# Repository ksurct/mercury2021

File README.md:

# mercury2021
KSURCT's repo for the 2021 OSU Mercury Robotics Challenge

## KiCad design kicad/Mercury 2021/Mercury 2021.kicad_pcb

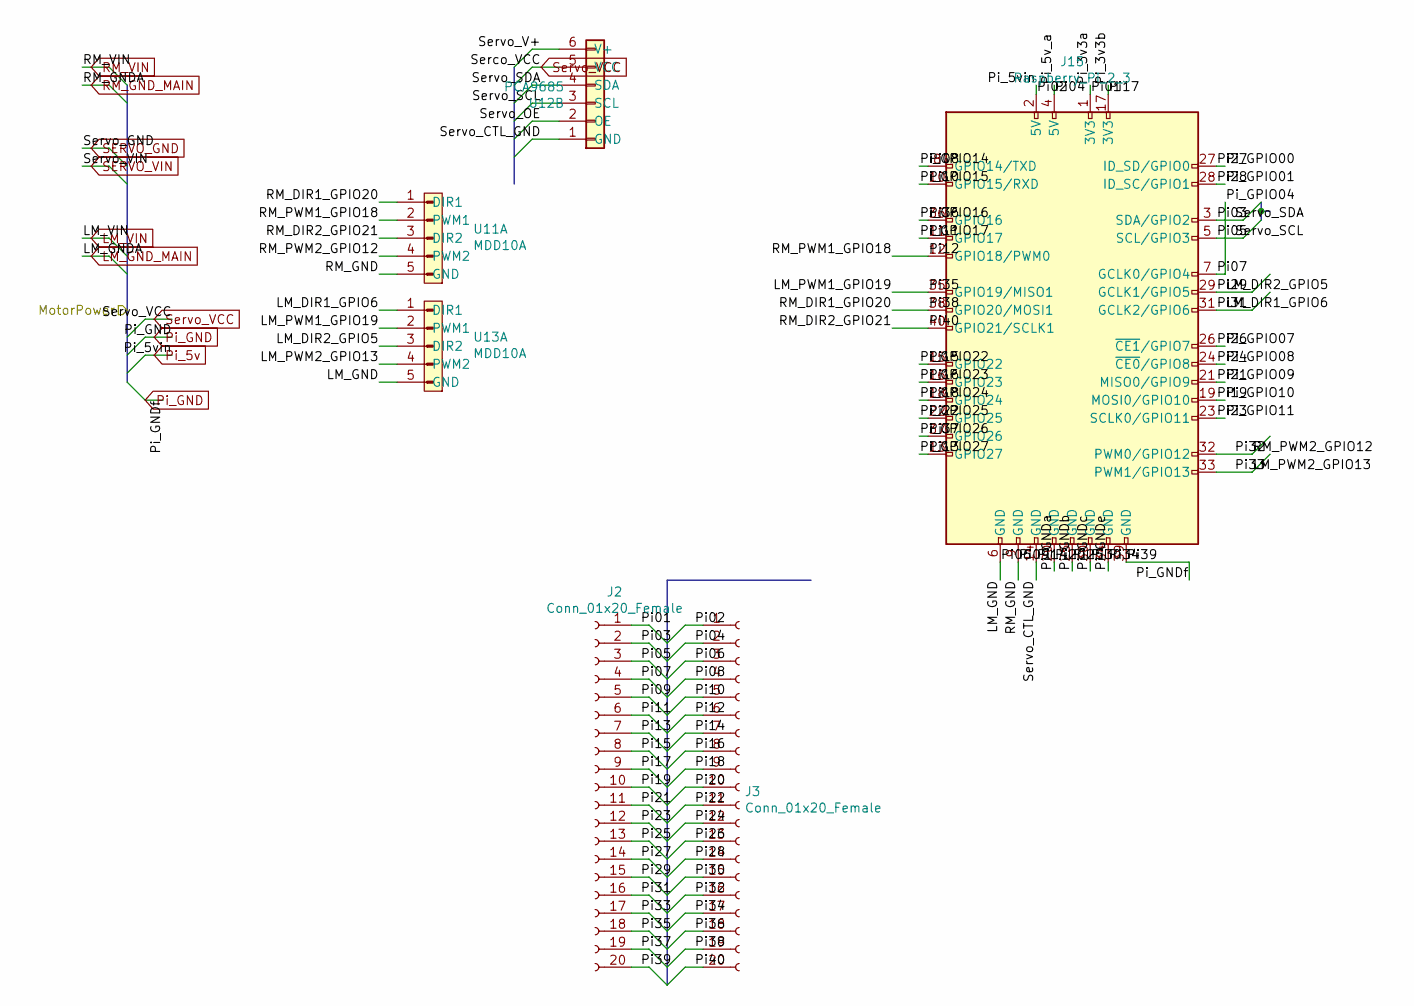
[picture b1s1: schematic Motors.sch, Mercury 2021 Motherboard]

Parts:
J2, J3: Conn_01x20_Female; PinSocket_1x20_P2.54mm_Vertical
J15: Raspberry_Pi_2_3; PinSocket_2x20_P2.54mm_Vertical
U11, U13: MDD10A; PinSocket_1x05_P2.54mm_Vertical
U12: PCA9685; PinSocket_1x06_P2.54mm_Vertical

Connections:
5v_Rail: J3.1, J15.2 (5V), U12.5 (VCC); also elsewhere on the board
/Motors/LM_DIR1_GPIO6: J2.16, J15.31 (GCLK2/GPIO6), U13.1 (DIR1)
/Motors/LM_DIR2_GPIO5: J2.15, J15.29 (GCLK1/GPIO5), U13.3 (DIR2)
/Motors/LM_GND: J3.3, J15.6 (GND), U13.5 (GND)
/Motors/LM_PWM1_GPIO19: J2.18, J15.35 (GPIO19/MISO1), U13.2 (PWM1)
/Motors/LM_PWM2_GPIO13: J2.17, J15.33 (PWM1/GPIO13), U13.4 (PWM2)
/Motors/Pi01: J2.1, J15.1 (3V3)
/Motors/Pi03: J2.2, J15.3 (SDA/GPIO2), U12.4 (SDA)
/Motors/Pi04: J3.2, J15.4 (5V)
/Motors/Pi05: J2.3, J15.5 (SCL/GPIO3), U12.3 (SCL)
/Motors/Pi07: J2.4, J15.7 (GCLK0/GPIO4)
/Motors/Pi08: J3.4, J15.8 (GPIO14/TXD)
/Motors/Pi09: J2.5, J15.9 (GND), U11.5 (GND)
/Motors/Pi10: J3.5, J15.10 (GPIO15/RXD)
/Motors/Pi11: J2.6, J15.11 (GPIO17)
/Motors/Pi12: J3.6, J15.12 (GPIO18/PWM0), U11.2 (PWM1)
/Motors/Pi13: J2.7, J15.13 (GPIO27)
/Motors/Pi14: J3.7, J15.14 (GND), U12.1 (GND)
/Motors/Pi15: J2.8, J15.15 (GPIO22)
/Motors/Pi16: J3.8, J15.16 (GPIO23)
/Motors/Pi17: J2.9, J15.17 (3V3)
/Motors/Pi18: J3.9, J15.18 (GPIO24)
/Motors/Pi19: J2.10, J15.19 (MOSI0/GPIO10)
/Motors/Pi20: J3.10, J15.20 (GND)
/Motors/Pi21: J2.11, J15.21 (MISO0/GPIO9)
/Motors/Pi22: J3.11, J15.22 (GPIO25)
/Motors/Pi23: J2.12, J15.23 (SCLK0/GPIO11)
/Motors/Pi24: J3.12, J15.24 (~CE0~/GPIO8)
/Motors/Pi25: J2.13, J15.25 (GND)
/Motors/Pi26: J3.13, J15.26 (~CE1~/GPIO7)
/Motors/Pi27: J2.14, J15.27 (ID_SD/GPIO0)
/Motors/Pi28: J3.14, J15.28 (ID_SC/GPIO1)
/Motors/Pi30: J3.15, J15.30 (GND)
/Motors/Pi32: J3.16, J15.32 (PWM0/GPIO12), U11.4 (PWM2)
/Motors/Pi34: J3.17, J15.34 (GND)
/Motors/Pi36: J3.18, J15.36 (GPIO16)
/Motors/Pi37: J2.19, J15.37 (GPIO26)
/Motors/Pi38: J3.19, J15.38 (GPIO20/MOSI1), U11.1 (DIR1)
/Motors/Pi40: J3.20, J15.40 (GPIO21/SCLK1), U11.3 (DIR2)
/Motors/Servo_OE: U12.2 (OE)
/Motors/Servo_V+: U12.6 (V+)
GND_Rail: J2.20, J15.39 (GND); also elsewhere on the board

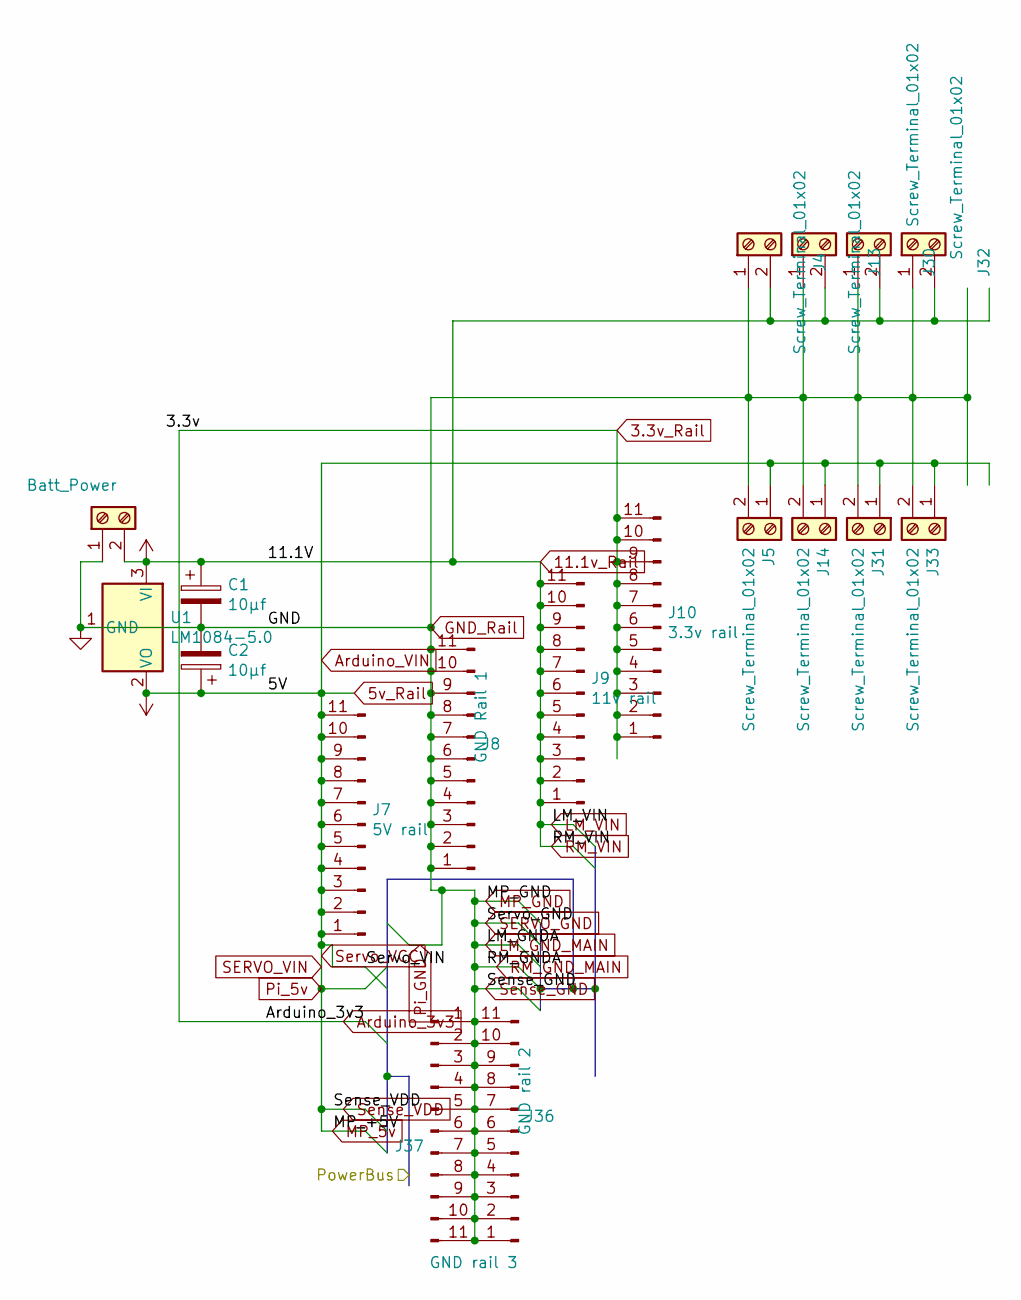
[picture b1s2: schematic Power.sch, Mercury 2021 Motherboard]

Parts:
C1, C2: 10μf; CP_Radial_D10.0mm_P2.50mm
J1: Batt_Power; TerminalBlock_Altech_AK300-2_P5.00mm
J4, J5, J13, J14, J30, J31, J32, J33: Screw_Terminal_01x02; TerminalBlock_Altech_AK300-2_P5.00mm
J7: 5V rail; PinHeader_1x11_P2.54mm_Vertical
J8: GND Rail 1; PinHeader_1x11_P2.54mm_Vertical
J9: 11v rail; PinHeader_1x11_P2.54mm_Vertical
J10: 3.3v rail; PinHeader_1x11_P2.54mm_Vertical
J36: GND rail 2; PinHeader_1x11_P2.54mm_Vertical
J37: GND rail 3; PinHeader_1x11_P2.54mm_Vertical
U1: LM1084-5.0; LM1084

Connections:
3.3v_Rail: J10.1, J10.2, J10.3, J10.4, J10.5, J10.6, J10.7, J10.8, J10.9, J10.10, J10.11; also elsewhere on the board
5v_Rail: C2.1, J5.1, J7.1, J7.2, J7.3, J7.4, J7.5, J7.6, J7.7, J7.8, J7.9, J7.10, J7.11, J14.1, J31.1, J33.1, U1.2 (VO); also elsewhere on the board
11.1v_Rail: C1.1, J1.2, J4.2, J9.1, J9.2, J9.3, J9.4, J9.5, J9.6, J9.7, J9.8, J9.9, J9.10, J9.11, J13.2, J30.2, J32.2, U1.3 (VI)
GND_Rail: C1.2, C2.2, J1.1, J4.1, J5.2, J8.1, J8.2, J8.3, J8.4, J8.5, J8.6, J8.7, J8.8, J8.9, J8.10, J8.11, J13.1, J14.2, J30.1, J31.2, J32.1, J33.2, J36.1, J36.2, J36.3, J36.4, J36.5, J36.6, J36.7, J36.8, J36.9, J36.10, J36.11, J37.1, J37.2, J37.3, J37.4, J37.5, J37.6, J37.7, J37.8, J37.9, J37.10, J37.11, U1.1 (GND); also elsewhere on the board

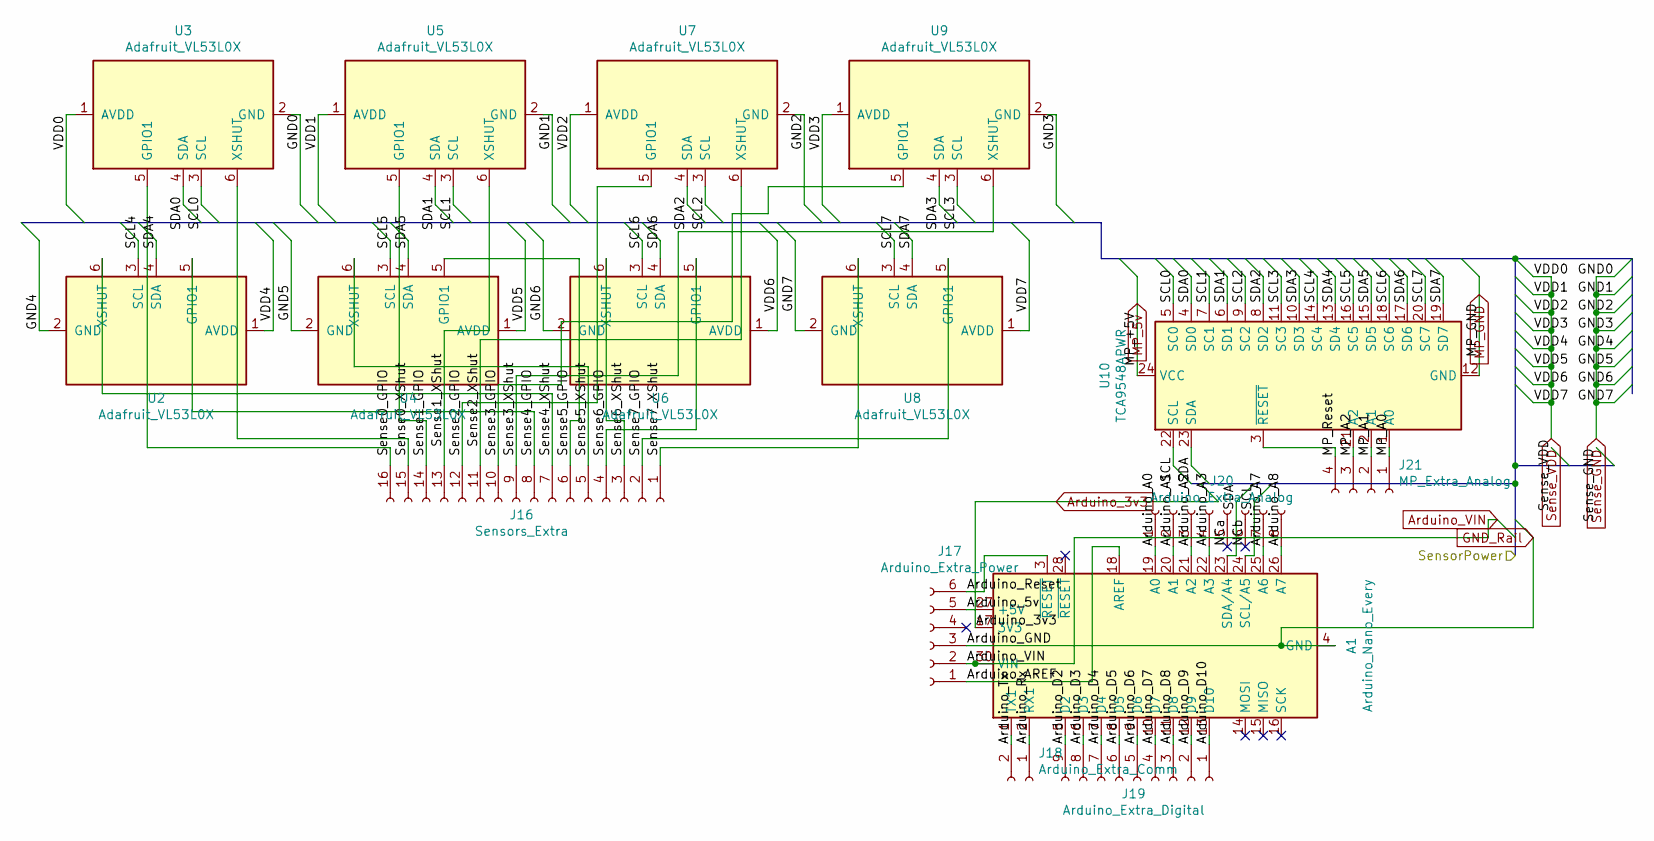
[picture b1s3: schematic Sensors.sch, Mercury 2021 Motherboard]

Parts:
A1: Arduino_Nano_Every; Arduino_Nano_WithMountingHoles
J16: Sensors_Extra; PinSocket_1x16_P2.54mm_Vertical
J17: Arduino_Extra_Power; PinSocket_1x06_P2.54mm_Vertical
J18: Arduino_Extra_Comm; PinSocket_1x02_P2.54mm_Vertical
J19: Arduino_Extra_Digital; PinSocket_1x09_P2.54mm_Vertical
J20: Arduino_Extra_Analog; PinSocket_1x08_P2.54mm_Vertical
J21: MP_Extra_Analog; PinSocket_1x04_P2.54mm_Vertical
U2, U3, U4, U5, U6, U7, U8, U9: Adafruit_VL53L0X; VL53L0X
U10: TCA9548APWR; TCA9548

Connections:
3.3v_Rail: A1.17 (3V3); also elsewhere on the board
5v_Rail: A1.30 (VIN), J17.2, U2.1 (AVDD), U3.1 (AVDD), U4.1 (AVDD), U5.1 (AVDD), U6.1 (AVDD), U7.1 (AVDD), U8.1 (AVDD), U9.1 (AVDD), U10.24 (VCC); also elsewhere on the board
/Sensors/Arduino_5v: A1.27 (+5V), J17.5
/Sensors/Arduino_A0: A1.19 (A0), J20.1
/Sensors/Arduino_A1: A1.20 (A1), J20.2
/Sensors/Arduino_A2: A1.21 (A2), J20.3
/Sensors/Arduino_A3: A1.22 (A3), J20.4
/Sensors/Arduino_A7: A1.25 (A6), J20.7
/Sensors/Arduino_A8: A1.26 (A7), J20.8
/Sensors/Arduino_AREF: A1.18 (AREF), J17.1
/Sensors/Arduino_D2: A1.5 (D2), J19.9
/Sensors/Arduino_D3: A1.6 (D3), J19.8
/Sensors/Arduino_D4: A1.7 (D4), J19.7
/Sensors/Arduino_D5: A1.8 (D5), J19.6
/Sensors/Arduino_D6: A1.9 (D6), J19.5
/Sensors/Arduino_D7: A1.10 (D7), J19.4
/Sensors/Arduino_D8: A1.11 (D8), J19.3
/Sensors/Arduino_D9: A1.12 (D9), J19.2
/Sensors/Arduino_D10: A1.13 (D10), J19.1
/Sensors/Arduino_Reset: A1.3 (~RESET), J17.6
/Sensors/Arduino_Rx: A1.2 (RX1), J18.1
/Sensors/Arduino_Tx: A1.1 (TX1), J18.2
/Sensors/MP_A0: J21.1, U10.1 (A0)
/Sensors/MP_A1: J21.2, U10.2 (A1)
/Sensors/MP_A2: J21.3, U10.21 (A2)
/Sensors/MP_Reset: J21.4, U10.3 (~RESET)
/Sensors/NCa: J20.5
/Sensors/NCb: J20.6
/Sensors/SCL: A1.24 (SCL/A5), U10.22 (SCL)
/Sensors/SCL0: U3.3 (SCL), U10.5 (SC0)
/Sensors/SCL1: U5.3 (SCL), U10.7 (SC1)
/Sensors/SCL2: U7.3 (SCL), U10.9 (SC2)
/Sensors/SCL3: U9.3 (SCL), U10.11 (SC3)
/Sensors/SCL4: U2.3 (SCL), U10.14 (SC4)
/Sensors/SCL5: U4.3 (SCL), U10.16 (SC5)
/Sensors/SCL6: U6.3 (SCL), U10.18 (SC6)
/Sensors/SCL7: U8.3 (SCL), U10.20 (SC7)
/Sensors/SDA: A1.23 (SDA/A4), U10.23 (SDA)
/Sensors/SDA0: U3.4 (SDA), U10.4 (SD0)
/Sensors/SDA1: U5.4 (SDA), U10.6 (SD1)
/Sensors/SDA2: U7.4 (SDA), U10.8 (SD2)
/Sensors/SDA3: U9.4 (SDA), U10.10 (SD3)
/Sensors/SDA4: U2.4 (SDA), U10.13 (SD4)
/Sensors/SDA5: U4.4 (SDA), U10.15 (SD5)
/Sensors/SDA6: U6.4 (SDA), U10.17 (SD6)
/Sensors/SDA7: U8.4 (SDA), U10.19 (SD7)
/Sensors/Sense0_GPIO: J16.16, U3.5 (GPIO1)
/Sensors/Sense0_XShut: J16.15, U3.6 (XSHUT)
/Sensors/Sense1_GPIO: J16.14, U5.5 (GPIO1)
/Sensors/Sense1_XShut: J16.13, U5.6 (XSHUT)
/Sensors/Sense2_GPIO: J16.12, U7.5 (GPIO1)
/Sensors/Sense2_XShut: J16.11, U7.6 (XSHUT)
/Sensors/Sense3_GPIO: J16.10, U9.5 (GPIO1)
/Sensors/Sense3_XShut: J16.9, U9.6 (XSHUT)
/Sensors/Sense4_GPIO: J16.8, U2.5 (GPIO1)
/Sensors/Sense4_XShut: J16.7, U2.6 (XSHUT)
/Sensors/Sense5_GPIO: J16.6, U4.5 (GPIO1)
/Sensors/Sense5_XShut: J16.5, U4.6 (XSHUT)
/Sensors/Sense6_GPIO: J16.4, U6.5 (GPIO1)
/Sensors/Sense6_XShut: J16.3, U6.6 (XSHUT)
/Sensors/Sense7_GPIO: J16.2, U8.5 (GPIO1)
/Sensors/Sense7_XShut: J16.1, U8.6 (XSHUT)
GND_Rail: A1.4 (GND), A1.29 (GND), J17.3, U2.2 (GND), U3.2 (GND), U4.2 (GND), U5.2 (GND), U6.2 (GND), U7.2 (GND), U8.2 (GND), U9.2 (GND), U10.12 (GND); also elsewhere on the board

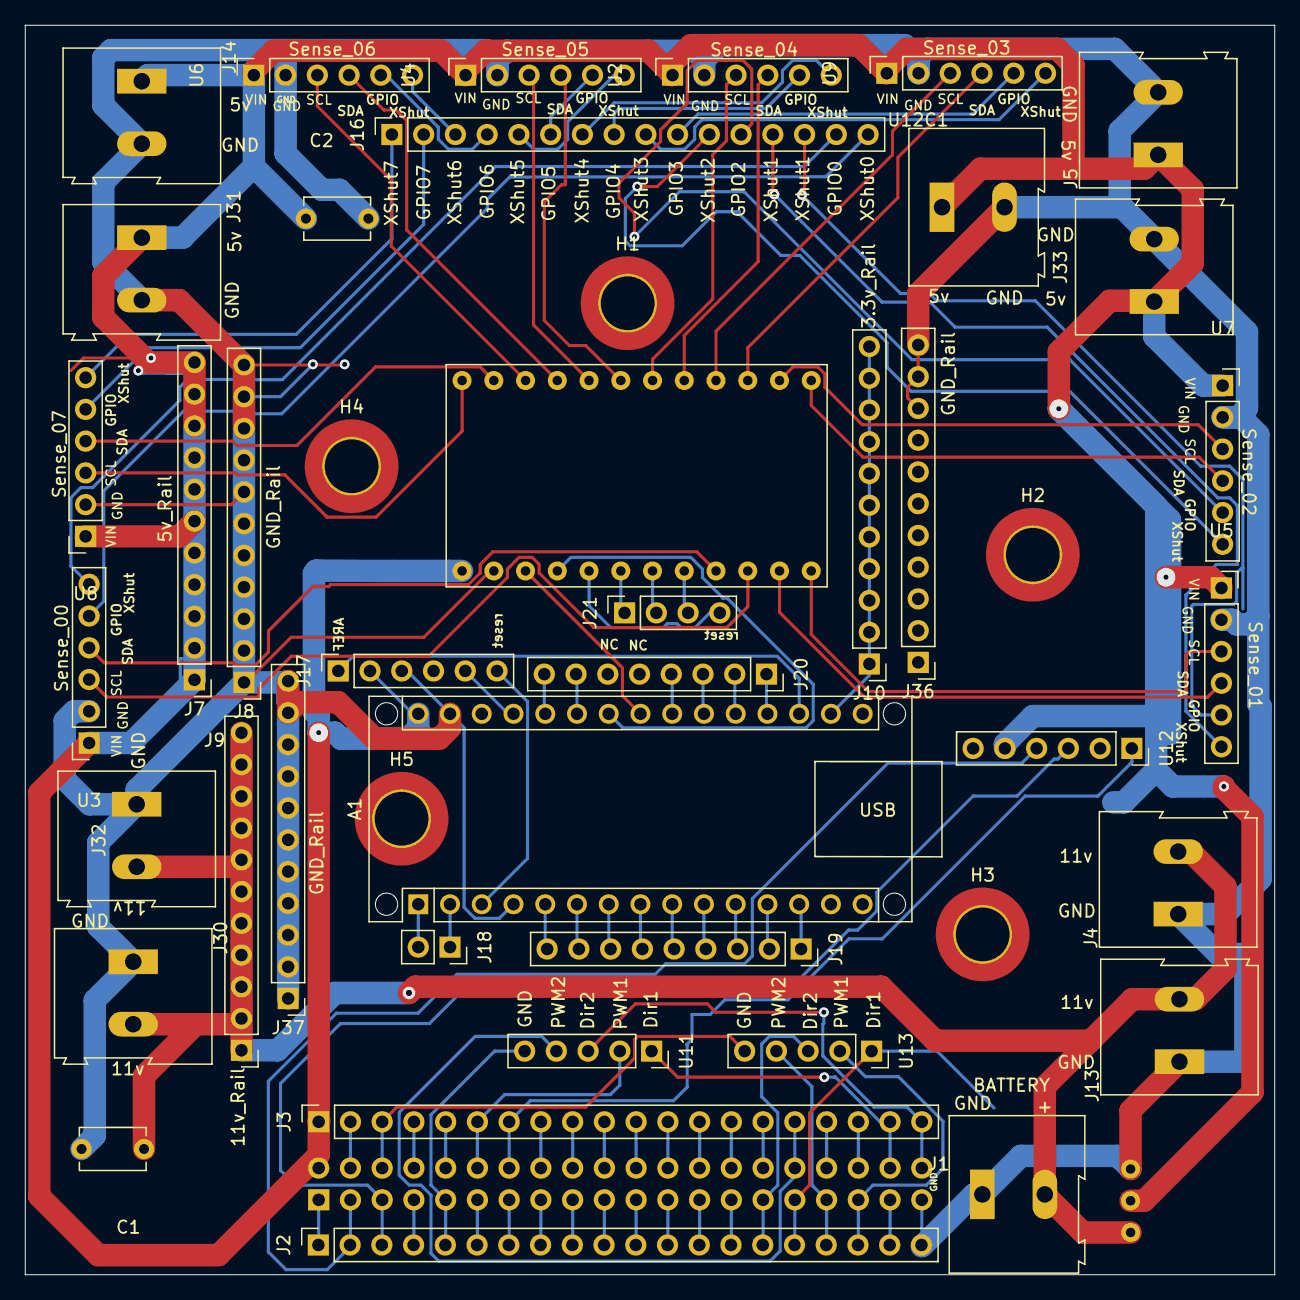
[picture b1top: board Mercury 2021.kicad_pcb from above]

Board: 2 copper layers, 100.0 x 100.0 mm, 46 parts (1 on the bottom side), 100 nets.

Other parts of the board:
H1, H2, H3, H4, H5: MountingHole; MountingHole_4.3mm_M4_DIN965_Pad_TopBottom
U12C1: PCA9685; TerminalBlock_Altech_AK300-2_P5.00mm

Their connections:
5v_Rail: U12C1.1; also elsewhere on the board
GND_Rail: U12C1.2; also elsewhere on the board

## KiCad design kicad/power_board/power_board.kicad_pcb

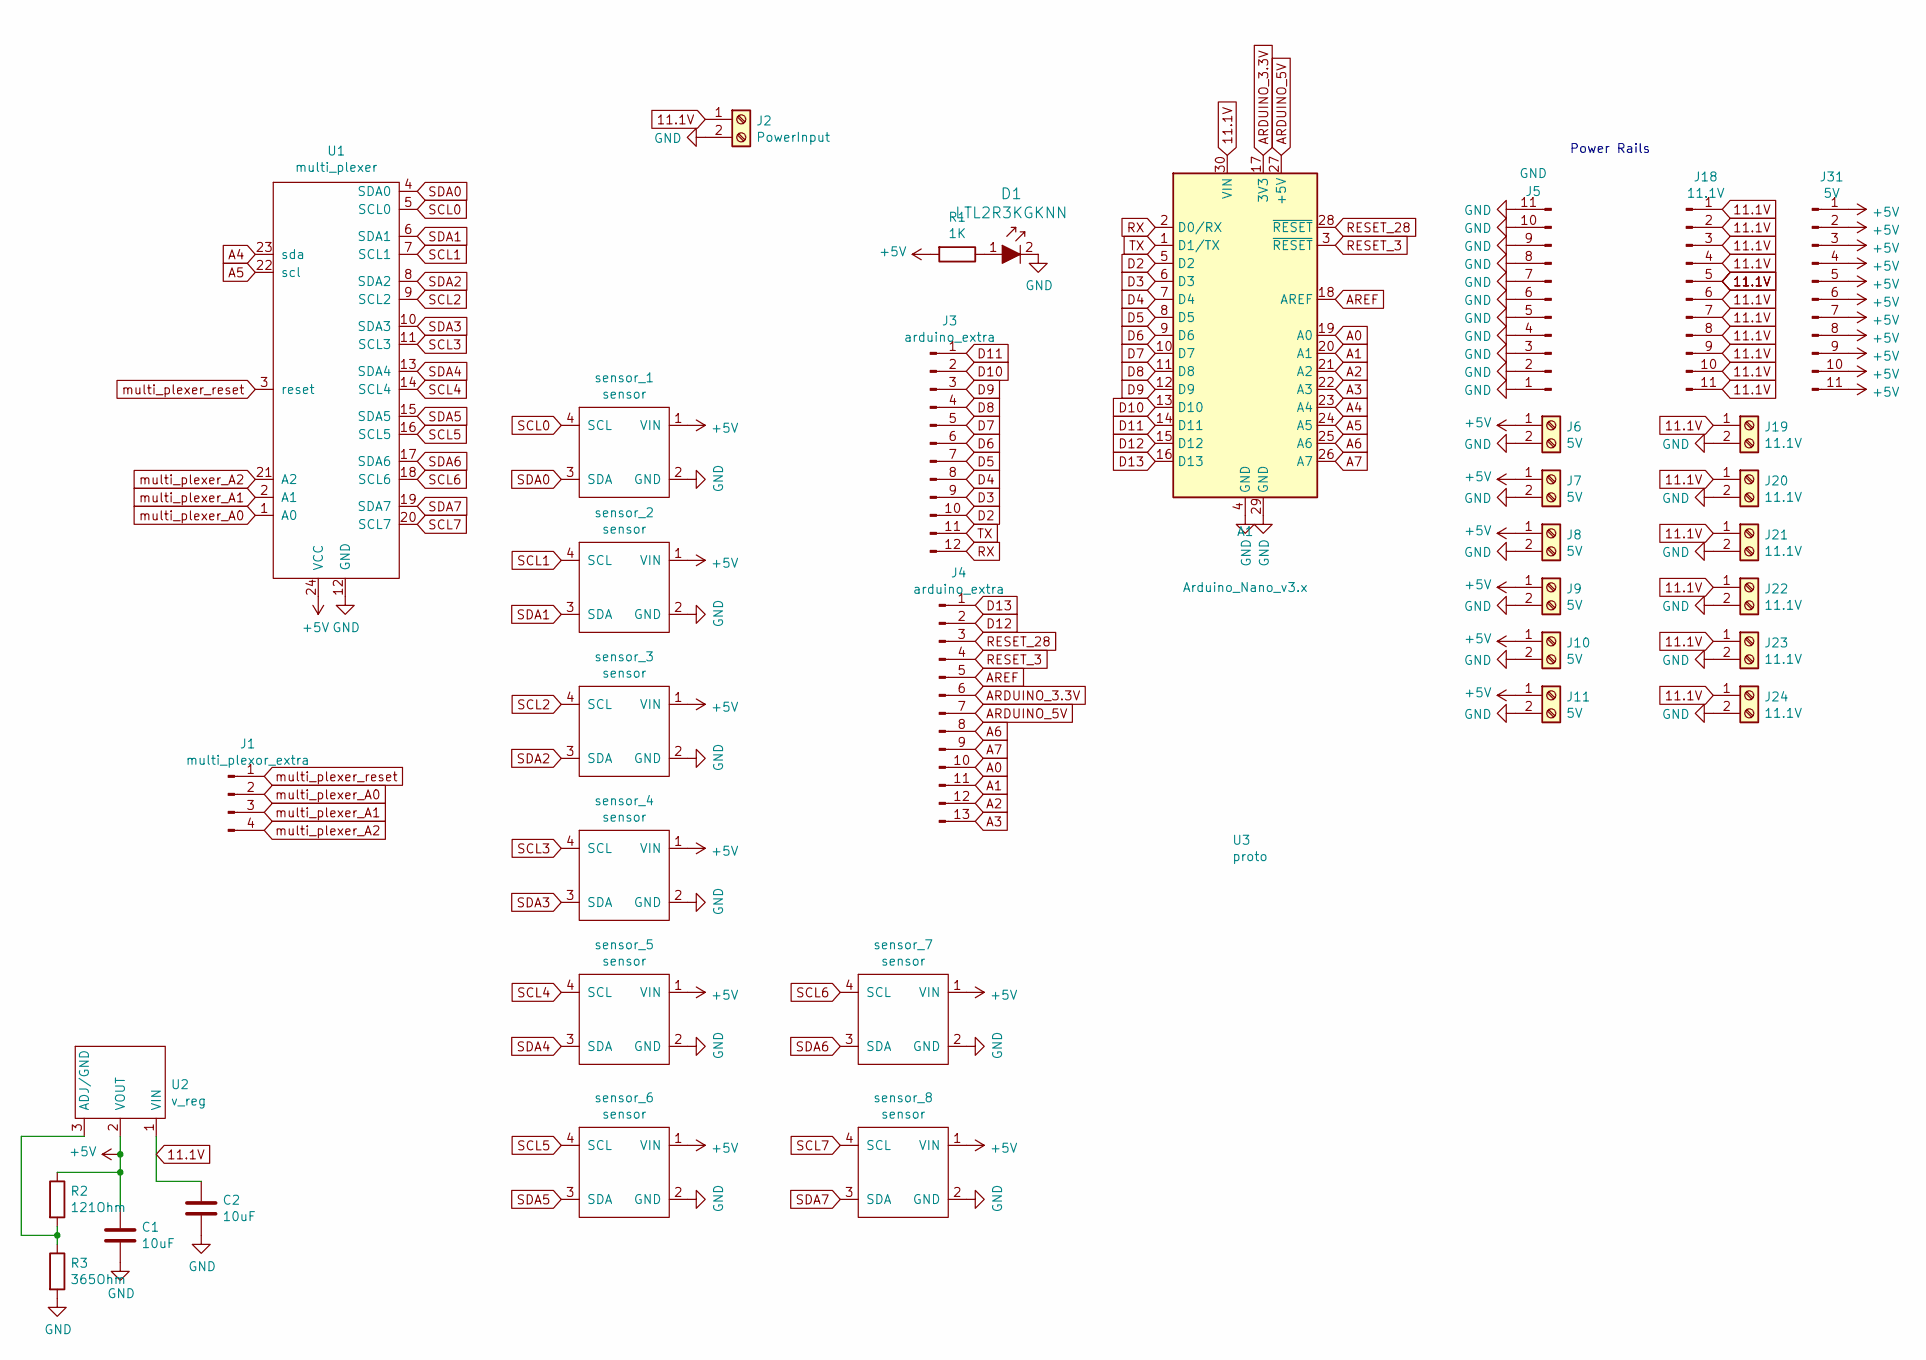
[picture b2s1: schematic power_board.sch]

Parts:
A1: Arduino_Nano_v3.x; Arduino_Nano
C1, C2: 10uF; C_Disc_D4.7mm_W2.5mm_P5.00mm
D1: LTL2R3KGKNN; LED_5mm_Radial; MPN LTL2R3KGKNN; Digi-Key_PN 160-1947-ND
J1: multi_plexor_extra; PinHeader_1x04_P2.54mm_Vertical
J2: PowerInput; 11.1V_block
J3: arduino_extra; PinHeader_1x12_P2.54mm_Vertical
J4: arduino_extra; PinHeader_1x13_P2.54mm_Vertical
J5: GND; PinHeader_1x11_P2.54mm_Vertical
J6, J7, J8, J9, J10, J11: 5V; 5v_BLOCK
J18: 11.1V; PinHeader_1x11_P2.54mm_Vertical
J19, J20, J21, J22, J23, J24: 11.1V; 11.1V_block
J31: 5V; PinHeader_1x11_P2.54mm_Vertical
R1: 1K; R_Axial_DIN0204_L3.6mm_D1.6mm_P7.62mm_Horizontal
R2: 121Ohm; R_Axial_DIN0204_L3.6mm_D1.6mm_P7.62mm_Horizontal
R3: 365Ohm; R_Axial_DIN0204_L3.6mm_D1.6mm_P7.62mm_Horizontal
U1: multi_plexer; multi_plexor
U2: v_reg
U3: proto
sensor_1, sensor_2, sensor_3, sensor_4, sensor_5, sensor_6, sensor_7, sensor_8: sensor

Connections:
11.1V: A1.30 (VIN), C2.1, J2.1, J18.1, J18.2, J18.3, J18.4, J18.5, J18.6, J18.7, J18.8, J18.9, J18.10, J18.11, J19.1, J20.1, J21.1, J22.1, J23.1, J24.1, U2.1 (VIN)
+5V: C1.1, J6.1, J7.1, J8.1, J9.1, J10.1, J11.1, J31.1, J31.2, J31.3, J31.4, J31.5, J31.6, J31.7, J31.8, J31.9, J31.10, J31.11, R1.2, R2.1, U1.24 (VCC), U2.2 (VOUT), sensor_1.1 (VIN), sensor_2.1 (VIN), sensor_3.1 (VIN), sensor_4.1 (VIN), sensor_5.1 (VIN), sensor_6.1 (VIN), sensor_7.1 (VIN), sensor_8.1 (VIN)
A0: A1.19 (A0), J4.10
A1: A1.20 (A1), J4.11
A2: A1.21 (A2), J4.12
A3: A1.22 (A3), J4.13
A4: A1.23 (A4), U1.23 (sda)
A5: A1.24 (A5), U1.22 (scl)
A6: A1.25 (A6), J4.8
A7: A1.26 (A7), J4.9
ARDUINO_3.3V: A1.17 (3V3), J4.6
ARDUINO_5V: A1.27 (+5V), J4.7
AREF: A1.18 (AREF), J4.5
D2: A1.5 (D2), J3.10
D3: A1.6 (D3), J3.9
D4: A1.7 (D4), J3.8
D5: A1.8 (D5), J3.7
D6: A1.9 (D6), J3.6
D7: A1.10 (D7), J3.5
D8: A1.11 (D8), J3.4
D9: A1.12 (D9), J3.3
D10: A1.13 (D10), J3.2
D11: A1.14 (D11), J3.1
D12: A1.15 (D12), J4.2
D13: A1.16 (D13), J4.1
GND: A1.4 (GND), A1.29 (GND), C1.2, C2.2, D1.2, J2.2, J5.1, J5.2, J5.3, J5.4, J5.5, J5.6, J5.7, J5.8, J5.9, J5.10, J5.11, J6.2, J7.2, J8.2, J9.2, J10.2, J11.2, J19.2, J20.2, J21.2, J22.2, J23.2, J24.2, R3.2, U1.12 (GND), sensor_1.2 (GND), sensor_2.2 (GND), sensor_3.2 (GND), sensor_4.2 (GND), sensor_5.2 (GND), sensor_6.2 (GND), sensor_7.2 (GND), sensor_8.2 (GND)
unnamed: D1.1, R1.1
unnamed: R2.2, R3.1, U2.3 (ADJ/GND)
RESET_3: A1.3 (~RESET), J4.4
RESET_28: A1.28 (~RESET), J4.3
RX: A1.2 (D0/RX), J3.12
SCL0: U1.5 (SCL0), sensor_1.4 (SCL)
SCL1: U1.7 (SCL1), sensor_2.4 (SCL)
SCL2: U1.9 (SCL2), sensor_3.4 (SCL)
SCL3: U1.11 (SCL3), sensor_4.4 (SCL)
SCL4: U1.14 (SCL4), sensor_5.4 (SCL)
SCL5: U1.16 (SCL5), sensor_6.4 (SCL)
SCL6: U1.18 (SCL6), sensor_7.4 (SCL)
SCL7: U1.20 (SCL7), sensor_8.4 (SCL)
SDA0: U1.4 (SDA0), sensor_1.3 (SDA)
SDA1: U1.6 (SDA1), sensor_2.3 (SDA)
SDA2: U1.8 (SDA2), sensor_3.3 (SDA)
SDA3: U1.10 (SDA3), sensor_4.3 (SDA)
SDA4: U1.13 (SDA4), sensor_5.3 (SDA)
SDA5: U1.15 (SDA5), sensor_6.3 (SDA)
SDA6: U1.17 (SDA6), sensor_7.3 (SDA)
SDA7: U1.19 (SDA7), sensor_8.3 (SDA)
TX: A1.1 (D1/TX), J3.11
multi_plexer_A0: J1.2, U1.1 (A0)
multi_plexer_A1: J1.3, U1.2 (A1)
multi_plexer_A2: J1.4, U1.21 (A2)
multi_plexer_reset: J1.1, U1.3 (reset)

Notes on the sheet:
Power Rails

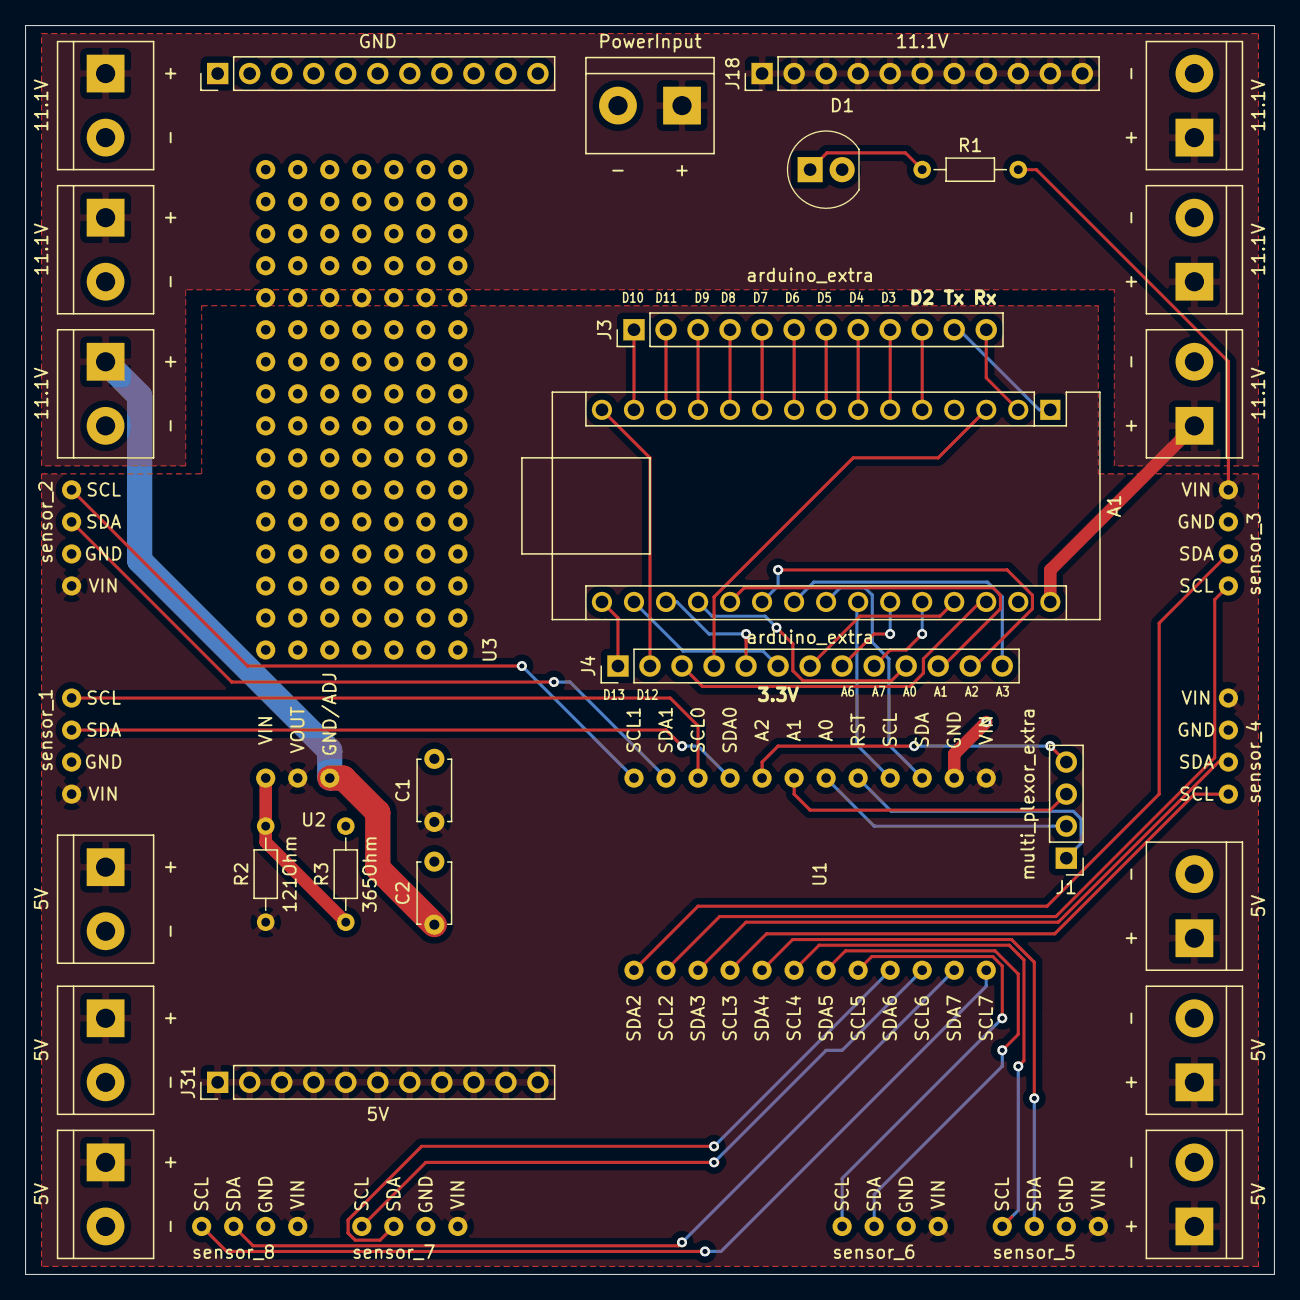
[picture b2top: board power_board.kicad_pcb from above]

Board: 2 copper layers, 99.1 x 99.1 mm, 37 parts (0 on the bottom side), 52 nets.

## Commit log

2019-09-26 Added explanation files in each base level folder. Added Point.py and ObstacleField.py
2019-09-26 added ObstacleGenerator
2019-09-26 This is the start of the path finder
2019-09-26 Random Change
2019-09-27 Made change
2019-09-27 Completed toString. ObstacleField now prints out.
2019-09-27 Removed unnecessary comment
2019-09-27 Added Functionality to ObstacleGenerator
2019-09-27 Added documentation and default arguments to ObstacleField.py
2019-09-27 Removed doubled points and improved self collision function
2019-10-01 Added convertToArray function
2019-10-01 Add gitignore file
2019-10-03 Added CsvHandler for loading and saving ObstacleField's to csv files
2019-10-04 Added walls and entrances to test array
2019-10-04 Added another point to example
2019-10-04 Added another point on example
2019-10-04 This is the first untested version of the PathFinder
2019-10-04 fixed a non python syntaxicall thingy
2019-10-04 this thing now compiles
2019-10-07 Made it sort of work
2019-10-08 made stuff work
2019-10-08 made more fixes
2019-10-08 implemented pathfinder into obstaclegenerator
2019-10-08 This is something
2019-10-08 made changes
2019-10-08 Added invertedarray property
2019-10-14 this is a bunc of stuff
2019-10-14 Implemented pathchecker into generator
2019-10-15 Add files via upload
    Creates heat maps from a csv file
2019-10-17 Very initial web server
2019-10-17 Add Pi hat designs
    Added a folder and schemitics for the pi and arduino connections
2019-10-18 Create model for controller on web server
2019-10-21 path checker is now working good
2019-10-21 minor changes
2019-10-21 Complete controller model and views on web server, including tests
2019-10-22 Added block diagram base.
2019-10-22 File generates large set of solvable courses
2019-10-22 Generates large set of solvable courses
2019-10-24 Added Buck converter and LEDs
    Added Buck converter symbol and LEDs to schematic
2019-11-01 Added simulator files
2019-11-04 THis is the commit for obsicle thing
2019-11-04 Added model
2019-11-04 This is the start of the robot model
2019-11-05 Added starting code for simulator in pygame
2019-11-05 Added RobotModel.py
2019-11-05 This is Trey's magnificant Algorithm class
2019-11-05 Adding these files from lab computer. Not sure who to credit.
2019-11-07 added functionality to RobotModel.moveFK()
2019-11-08 this is the addition of a sad implementation of the inverse kinematics
2019-11-08 percent errors have been added
2019-11-08 added the foreward keniatic model
2019-11-08 Fixed dumb trig in ICC
2019-11-08 this is the fixed version of the ternary
2019-11-09 Finished tutorials on creating top down racing game
2019-11-09 First pass at combining OOP and pygame. Going to backpedal and create a straighforward game first.
2019-11-09 Combined self.l and self.length
2019-11-14 Start HardwareModels file as example of code we can create for robot
2019-11-19 made oppy transparent
2019-11-19 Starting development on pyglet as replacement to pygame
2019-12-06 Added robot code
2019-12-06 Start of basestation code
2019-12-10 Updates to basestation
2019-12-10 Added solidworks models and drawings to repository
2019-12-10 added holes to chassis for motor support
2019-12-10 Started on DSP code
2019-12-19 added parts
2020-02-10 Add temp file for controlling robot using keyboard
2020-02-11 Adding holes to the chassis for the motor support
2020-02-14 Set up skeleton for keyboard control
2020-02-21 Added Solidworks parts
2020-02-25 This is the commit
2020-02-27 Added CAD Files
2020-02-27 This is the start of the pyglet stuff
2020-02-27 Added class to scale oFields
2020-02-27 Committing this as a pyglet / pygame deadend point.
2020-02-28 Added Tires and Junk
2020-03-03 This is the commit for the simulation software
2020-03-04 Work on hardware model code and keyboard input from pynput
2020-03-04 Some work on keyboard control
2020-03-05 Wheels move with keyboard
2020-03-05 Get rid of print statements that we don't need to look at anymore
2020-03-05 Add code to motor board
2020-09-23 Added stuff
2020-09-23 Added more
2020-09-23 modify assembly
2020-10-08 Depricated old items and added new folders / diagrams
2020-10-22 Made the robot control simulator
2020-10-23 Motor test
2020-10-23 More
2020-10-23 Added Motor Controls folder and ServoModel class
2020-10-23 keyboard
2020-10-23 Added functionality to ServoModel
2020-10-23 motor class
2020-10-23 cleaned things up a bit
2020-10-27 Romote keyboard
2020-11-13 Added a python module file structure and moved all existing files to the depricated folder to sort out later.'
2020-11-13 added empty readme files to every folder so they get committed to gitub
2020-11-16 Please enter the commit message for your changes. Lines starting
    moved old CAD files to depricated folder
2020-11-20 moved and added some CAD
2021-01-27 Added beginning of settings
2021-01-27 Added start of actually making the module system work.
2021-01-28 Refresh all things mercury.
    This add a module system to the python programs we
    have written, this needs to be updated and tested.
2021-01-28 Updated name cases of modules.
2021-01-28 Fixing issues.
2021-01-28 move
2021-01-28 test
2021-01-28 Fixed naming issues.
2021-01-29 Added general case arguments system with needed classes.
2021-01-29 Updated argument tool
2021-02-02 Added simple testing software
2021-02-03 Added hello print
2021-02-03 Some message
2021-02-03 Training
2021-02-03 I made a change!!!!
2021-02-03 I made a change!!!
2021-02-03 Quen Made changes
2021-02-03 Alli made a change this time!
2021-02-03 Quen made a change
2021-02-08 slight restructure to flatten the code base
2021-02-08 Flatten simulation
2021-02-10 Added stuff for webserver
2021-02-10 Webserver
2021-02-10 New motor system
2021-02-10 works with modules!
2021-02-10 Added some new functions, got the robot conrol integrated with motors.
2021-02-10 Added module support for the simulator
2021-02-11 Added requests
2021-02-11 Added google thing
2021-02-11 More code
2021-02-14 Created a new chassis and assembly
2021-02-14 Made a function in the robot controller to read a command string. Also added an empty function to set a motor's direction.
2021-02-15 modified runCommand function to support discrete movements
2021-02-15 Fixed multi set speed functions
2021-02-17 Added More webcode
2021-02-17 Fixing bugs
2021-02-17 Added server code
2021-02-17 Fixed motors
2021-02-17 Robot control
2021-02-17 Getting rid of first word.1
2021-02-17 Strip first term
2021-02-17 merging changes
2021-02-17 Made the webserver communication possible
2021-02-18 Sim work
2021-02-24 Added count to make it so that will not pull repeats
2021-02-25 Updating appscript
2021-02-25 I made a claw and arm assembly
2021-02-27 Added server
2021-03-03 servo run good
2021-03-04 Sim work fix
2021-03-04 Driver work, basic input
2021-03-10 Added support for not repeating commands
2021-03-10 Made some changes
2021-03-10 Updated To move ServoMotor
2021-03-10 Made Even more changes
2021-03-10 Fixed issue with ServoMotor
2021-03-10 I think it is finally done
2021-03-10 Finished Updating Servo Motors
2021-03-11 Added kicad board
2021-03-11 Tried Null string
2021-03-11 Added parts for the arm
2021-03-11 added
2021-03-16 Read Multiple Distance Sensors
2021-03-17 Xbox, internet coms
2021-03-17 More stuff
2021-03-18 iMOre
2021-03-18 iMOrew
2021-03-18 Sped up commands and added error handling
2021-03-18 Added parts for robot arm
2021-03-21 Added camera stream
2021-03-24 JsonTest
2021-03-24 test for quitting if lost connection
2021-03-30 Add critical error handeling
2021-03-31 did a thing
2021-03-31 Updated communication between ardunio and pi and the ability to get sensor data.
2021-03-31 Updated communication from arduino to pi and updated getSensorData function
2021-04-01 arduino things
2021-04-06 driver_main code that didn't push from laptop
2021-04-06 Reorganized driver_main work for use later
2021-04-06 Some interface work (in progress)
2021-04-07 continuing interface work for real robot control
2021-04-07 Added enable to JSON
2021-04-07 updated power board
2021-04-07 Added the sensor mount
    Just the sensor mount this time
2021-04-08 New schematic I'm working on, WIP.
    WIP, other schematic should used for now
2021-04-08 Updated GitIgnore
    Git now ignores the DS_Store (a MacOS metadata file) as well as files for the 'y' project in folder 't' I was experimenting with.
2021-04-08 modified cad files'
2021-04-08 Servo mount files
2021-04-13 About to test if GPIO communication between arduino and pi works
2021-04-14 to test communication
2021-04-14 Fixed error
2021-04-14 More mistakes fixed
2021-04-14 Error fixed
2021-04-14 Updated new board
2021-04-14 Updated new board
    Created a 3.3v rail
2021-04-14 Updated the new PCB (lots of notes)
    - added net
    - changed symbols
    - added footprints
    - added ability to put the pi -> arduino cable through the board
    - fixed global labels
    - named connectors
2021-04-15 Updated new board
    - Did PCB traces
    -- almost got away with just 2 copper layers, pi ruined it when there was only a bit to go. Probably possible but would take a lot of back and forth
2021-04-15 interface for sensor testing (work in prog)
2021-04-15 Cleaned up interface for driver_main
2021-04-16 New New board
2021-04-16 Updated board
2021-04-16 Update Mercury 2021.kicad_pcb-bak
2021-04-16 Switched to 2 layers
2021-04-16 Updated board
    Silk screen and mounting holes
2021-04-16 Updated board
    Made the regulator bigger
2021-04-16 Updated board
    Mounting holes
2021-04-16 Ordered the pcb
2021-04-19 Added servo arm control
2021-04-21 Fixed Errors
2021-04-21 This is good now
2021-04-22 Camera
2021-04-23 Fixed PCB
    Multiplexer Footprint fixed
2021-04-27 Added alot
2021-04-28 NOTE! Updated PCB
    This is different than the PCBs that were ordered.
2021-04-28 Updated PCB
    Updated Labels & arduino now powered off of board.
2021-04-28 sensor reading. yay
2021-04-29 it sends data, but not sure if sensor data
2021-04-29 Updated PCB
    Flipped connector around
2021-05-05 You have done good
2021-05-05 all the arrays are wrong
2021-05-06 Updated encoder (issue below)
    I think the speed should be good now, but the serial stopped working
2021-05-06 Encoder Speed
    it works now
2021-05-06 worked on the JSON
2021-05-07 Added skeleton for arduino code
2021-05-11 Fixed thing
2021-05-11 2 sensors work, hall effect work, interrupt signal works, all sent to json
